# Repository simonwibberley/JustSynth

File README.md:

# JustSynth
Just Intonation Polyphonic Synthesizer

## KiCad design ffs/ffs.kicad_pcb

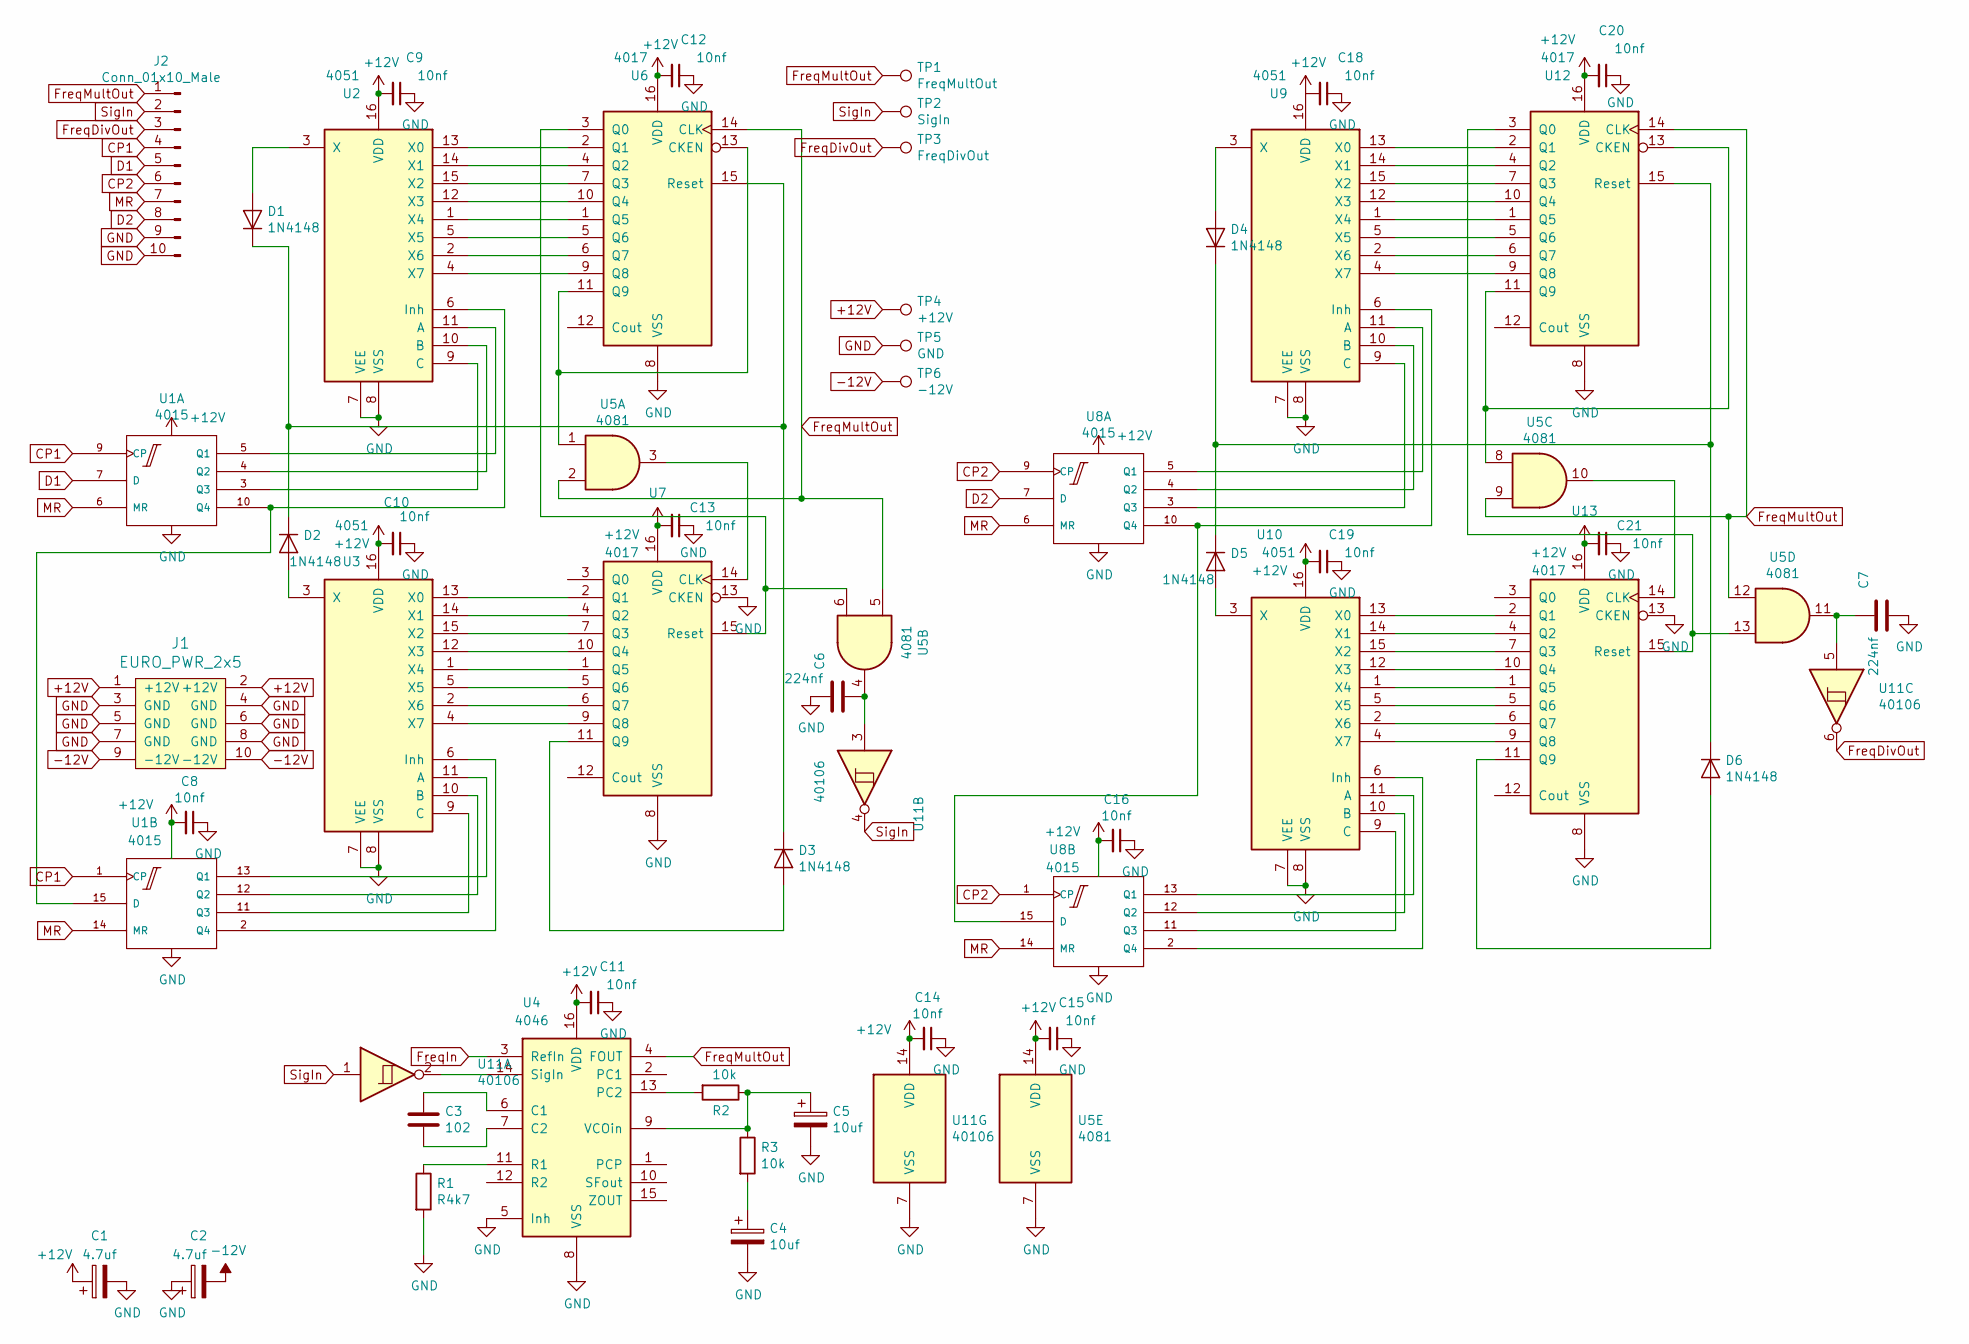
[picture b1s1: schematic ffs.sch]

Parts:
C1, C2: 4.7uf; CP_Radial_D8.0mm_P2.50mm
C3: 102; C_Disc_D4.3mm_W1.9mm_P5.00mm
C4, C5: 10uf; CP_Radial_D8.0mm_P2.50mm
C6, C7: 224nf; C_Disc_D4.3mm_W1.9mm_P5.00mm
C8, C9, C10, C11, C12, C13, C14, C15, C16, C18, C19, C20, C21: 10nf; C_1206_3216Metric_Pad1.42x1.75mm_HandSolder
D1, D2, D3, D4, D5, D6: 1N4148; D_DO-35_SOD27_P7.62mm_Horizontal
J1: EURO_PWR_2x5; IDC-Header_2x05_P2.54mm_Vertical
J2: Conn_01x10_Male; IDC-Header_2x05_P2.54mm_Vertical
R1: R4k7; R_Axial_DIN0207_L6.3mm_D2.5mm_P10.16mm_Horizontal
R2, R3: 10k; R_Axial_DIN0207_L6.3mm_D2.5mm_P10.16mm_Horizontal
TP1: FreqMultOut; TestPoint_Pad_2.5x2.5mm
TP2: SigIn; TestPoint_Pad_2.5x2.5mm
TP3: FreqDivOut; TestPoint_Pad_2.5x2.5mm
TP4: +12V; TestPoint_Pad_2.5x2.5mm
TP5: GND; TestPoint_Pad_2.5x2.5mm
TP6: -12V; TestPoint_Pad_2.5x2.5mm
U1, U8: 4015; DIP-16_W7.62mm_Socket
U2, U3, U9, U10: 4051; DIP-16_W7.62mm_Socket
U4: 4046; DIP-16_W7.62mm_Socket
U5: 4081; DIP-14_W7.62mm_Socket
U6, U7, U12, U13: 4017; DIP-16_W7.62mm_Socket
U11: 40106; DIP-16_W7.62mm_Socket

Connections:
+12V: C1.1, C8.2, C9.2, C10.2, C11.2, C12.2, C13.2, C14.2, C15.2, C16.2, C18.2, C19.2, C20.2, C21.2, J1.1 (+12V), J1.2 (+12V), TP4.1, U1.16 (Vdd), U2.16 (VDD), U3.16 (VDD), U4.16 (VDD), U5.14 (VDD), U6.16 (VDD), U7.16 (VDD), U8.16 (Vdd), U9.16 (VDD), U10.16 (VDD), U11.14 (VDD), U12.16 (VDD), U13.16 (VDD)
-12V: C2.2, J1.9 (-12V), J1.10 (-12V), TP6.1
CP1: J2.4, U1.1 (CP), U1.9 (CP)
CP2: J2.6, U8.1 (CP), U8.9 (CP)
D1: J2.5, U1.7 (D)
D2: J2.8, U8.7 (D)
FreqDivOut: J2.3, TP3.1, U11.6
FreqIn: U4.3 (RefIn)
FreqMultOut: J2.1, TP1.1, U4.4 (FOUT), U5.2, U5.5, U5.9, U5.12, U6.14 (CLK), U12.14 (CLK)
GND: C1.2, C2.1, C4.2, C5.2, C6.2, C7.1, C8.1, C9.1, C10.1, C11.1, C12.1, C13.1, C14.1, C15.1, C16.1, C18.1, C19.1, C20.1, C21.1, J1.3 (GND), J1.4 (GND), J1.5 (GND), J1.6 (GND), J1.7 (GND), J1.8 (GND), J2.9, J2.10, R1.2, TP5.1, U1.8 (Vss), U2.7 (VEE), U2.8 (VSS), U3.7 (VEE), U3.8 (VSS), U4.5 (Inh), U4.8 (VSS), U5.7 (VSS), U6.8 (VSS), U7.8 (VSS), U7.13 (CKEN), U8.8 (Vss), U9.7 (VEE), U9.8 (VSS), U10.7 (VEE), U10.8 (VSS), U11.7 (VSS), U12.8 (VSS), U13.8 (VSS), U13.13 (CKEN)
MR: J2.7, U1.6 (MR), U1.14 (MR), U8.6 (MR), U8.14 (MR)
unnamed: C3.1, U4.6 (C1)
unnamed: C3.2, U4.7 (C2)
unnamed: C4.1, R3.2
unnamed: C5.1, R2.1, R3.1, U4.9 (VCOin)
unnamed: C6.1, U5.4, U11.3
unnamed: C7.2, U5.11, U11.5
unnamed: D1.1 (K), D2.1 (K), D3.1 (K), U6.15 (Reset)
unnamed: D1.2 (A), U2.3 (X)
unnamed: D2.2 (A), U3.3 (X)
unnamed: D3.2 (A), U7.11 (Q9)
unnamed: D4.1 (K), D5.1 (K), D6.1 (K), U12.15 (Reset)
unnamed: D4.2 (A), U9.3 (X)
unnamed: D5.2 (A), U10.3 (X)
unnamed: D6.2 (A), U13.11 (Q9)
unnamed: R1.1, U4.11 (R1)
unnamed: R2.2, U4.13 (PC2)
unnamed: U1.2 (Q4), U3.6 (Inh)
unnamed: U1.3 (Q3), U2.9 (C)
unnamed: U1.4 (Q2), U2.10 (B)
unnamed: U1.5 (Q1), U2.11 (A)
unnamed: U1.10 (Q4), U1.15 (D), U2.6 (Inh)
unnamed: U1.11 (Q3), U3.9 (C)
unnamed: U1.12 (Q2), U3.10 (B)
unnamed: U1.13 (Q1), U3.11 (A)
unnamed: U2.1 (X4), U6.1 (Q5)
unnamed: U2.2 (X6), U6.6 (Q7)
unnamed: U2.4 (X7), U6.9 (Q8)
unnamed: U2.5 (X5), U6.5 (Q6)
unnamed: U2.12 (X3), U6.10 (Q4)
unnamed: U2.13 (X0), U6.2 (Q1)
unnamed: U2.14 (X1), U6.4 (Q2)
unnamed: U2.15 (X2), U6.7 (Q3)
unnamed: U3.1 (X4), U7.1 (Q5)
unnamed: U3.2 (X6), U7.6 (Q7)
unnamed: U3.4 (X7), U7.9 (Q8)
unnamed: U3.5 (X5), U7.5 (Q6)
unnamed: U3.12 (X3), U7.10 (Q4)
unnamed: U3.13 (X0), U7.2 (Q1)
unnamed: U3.14 (X1), U7.4 (Q2)
unnamed: U3.15 (X2), U7.7 (Q3)
unnamed: U5.1, U6.11 (Q9), U6.13 (CKEN)
unnamed: U5.3, U7.14 (CLK)
unnamed: U5.6, U6.3 (Q0), U7.15 (Reset)
unnamed: U8.3 (Q3), U9.9 (C)
unnamed: U8.4 (Q2), U9.10 (B)
unnamed: U8.5 (Q1), U9.11 (A)
unnamed: U8.10 (Q4), U8.15 (D), U9.6 (Inh)
unnamed: U10.1 (X4), U13.1 (Q5)
unnamed: U10.2 (X6), U13.6 (Q7)
unnamed: U10.4 (X7), U13.9 (Q8)
unnamed: U10.5 (X5), U13.5 (Q6)
unnamed: U8.2 (Q4), U10.6 (Inh)
unnamed: U8.11 (Q3), U10.9 (C)
unnamed: U8.12 (Q2), U10.10 (B)
unnamed: U8.13 (Q1), U10.11 (A)
unnamed: U10.12 (X3), U13.10 (Q4)
unnamed: U10.13 (X0), U13.2 (Q1)
unnamed: U10.14 (X1), U13.4 (Q2)
unnamed: U10.15 (X2), U13.7 (Q3)
unnamed: U4.14 (SigIn), U11.2
unnamed: U9.1 (X4), U12.1 (Q5)
unnamed: U9.13 (X0), U12.2 (Q1)
unnamed: U5.13, U12.3 (Q0), U13.15 (Reset)
unnamed: U9.14 (X1), U12.4 (Q2)
unnamed: U9.5 (X5), U12.5 (Q6)
unnamed: U9.2 (X6), U12.6 (Q7)
unnamed: U9.15 (X2), U12.7 (Q3)
unnamed: U9.4 (X7), U12.9 (Q8)
unnamed: U9.12 (X3), U12.10 (Q4)
unnamed: U5.8, U12.11 (Q9), U12.13 (CKEN)
unnamed: U5.10, U13.14 (CLK)
SigIn: J2.2, TP2.1, U11.1, U11.4

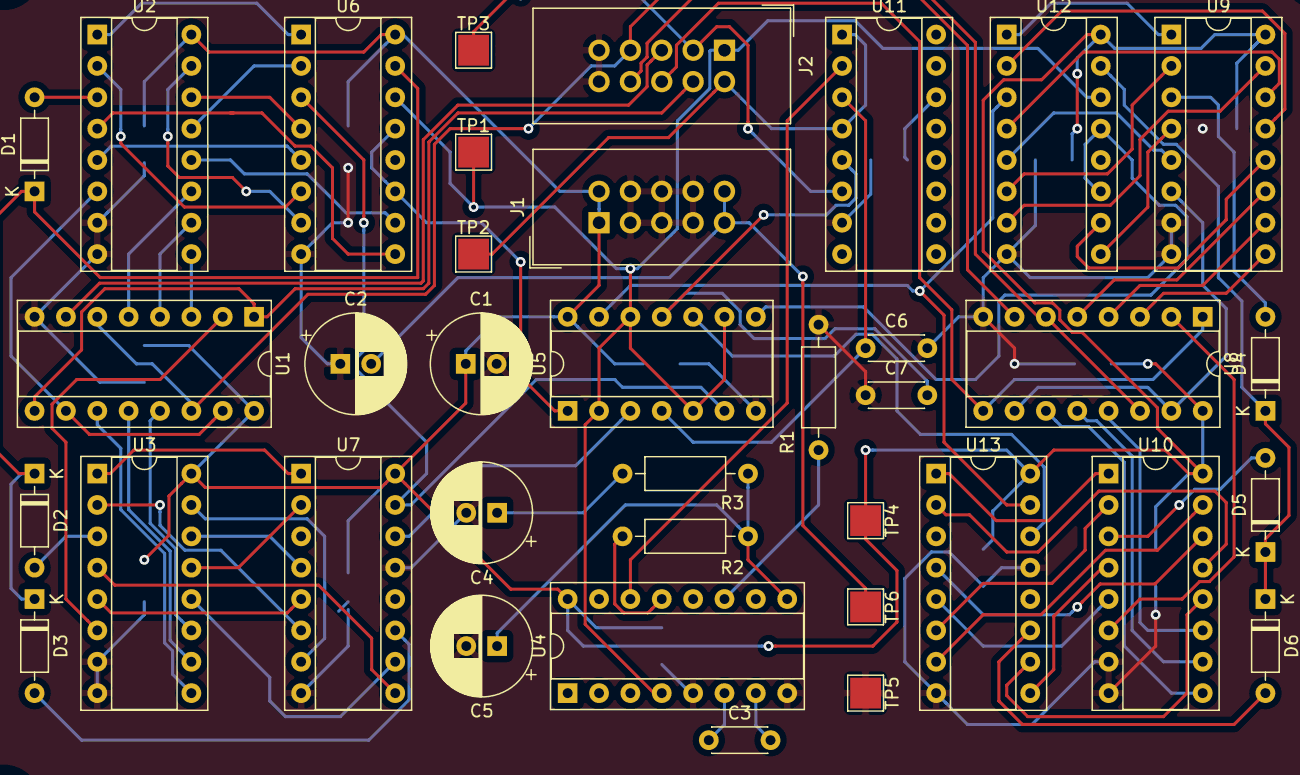
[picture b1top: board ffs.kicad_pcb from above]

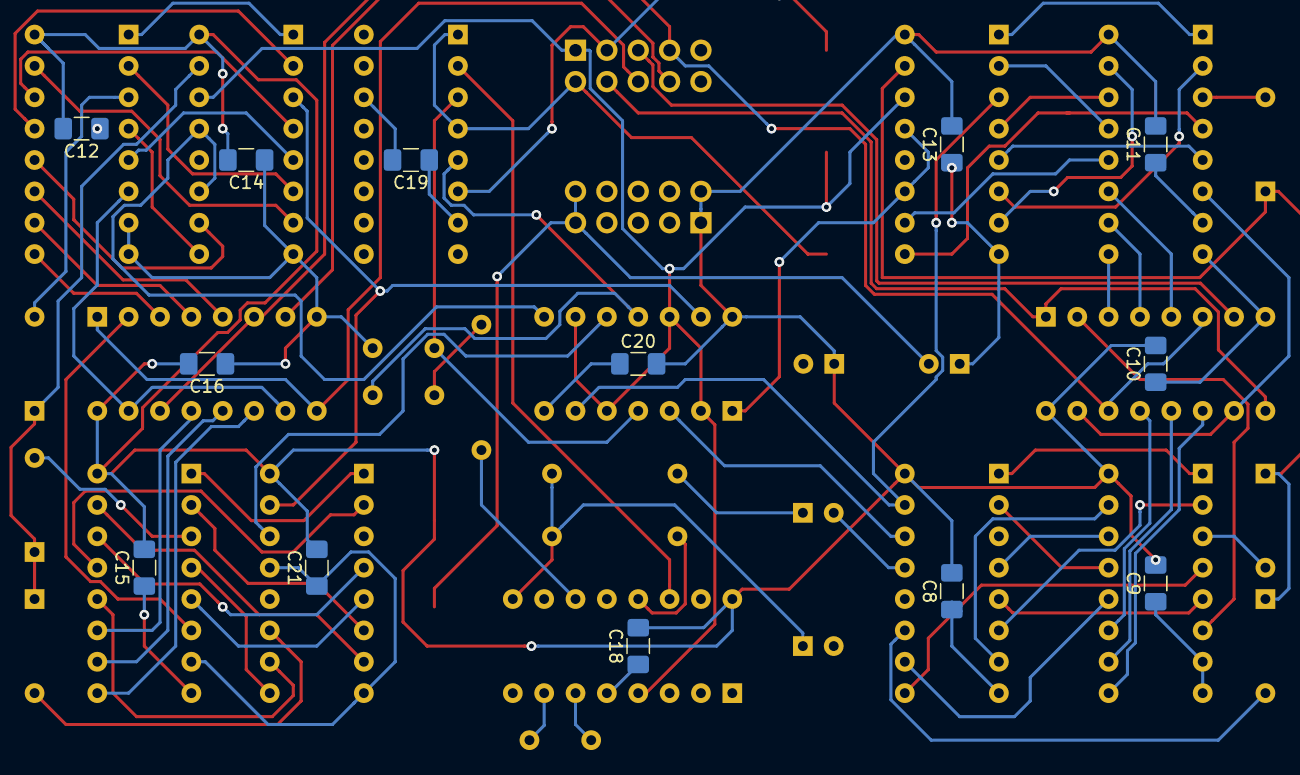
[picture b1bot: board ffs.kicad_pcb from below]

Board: 2 copper layers, 50 parts (13 on the bottom side), 82 nets.

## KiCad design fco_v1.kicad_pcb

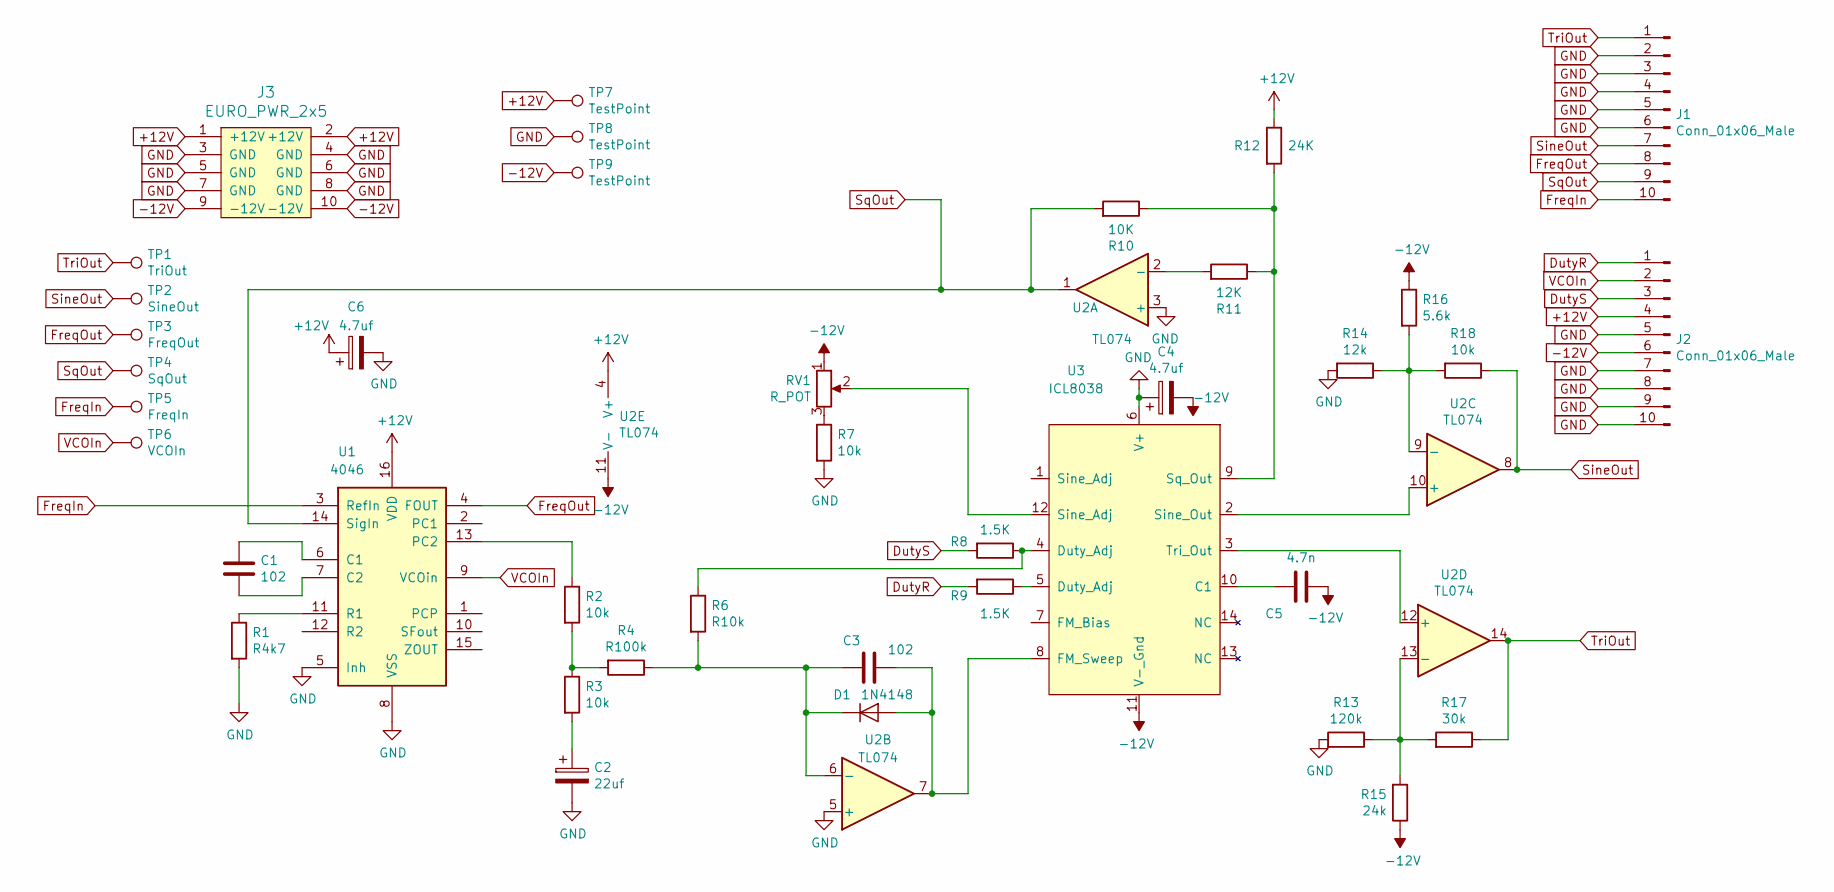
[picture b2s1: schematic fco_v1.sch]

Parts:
C1, C3: 102; C_Disc_D4.3mm_W1.9mm_P5.00mm
C2: 22uf; CP_Radial_D8.0mm_P2.50mm
C4, C6: 4.7uf; CP_Radial_D8.0mm_P2.50mm
C5: 4.7n; C_Disc_D4.3mm_W1.9mm_P5.00mm
D1: 1N4148; D_DO-35_SOD27_P7.62mm_Horizontal
J1, J2: Conn_01x06_Male; IDC-Header_2x05_P2.54mm_Vertical
J3: EURO_PWR_2x5; IDC-Header_2x05_P2.54mm_Vertical
R1: R4k7; R_Axial_DIN0207_L6.3mm_D2.5mm_P10.16mm_Horizontal
R2, R3, R7, R18: 10k; R_Axial_DIN0207_L6.3mm_D2.5mm_P10.16mm_Horizontal
R4: R100k; R_Axial_DIN0207_L6.3mm_D2.5mm_P10.16mm_Horizontal
R6: R10k; R_Axial_DIN0207_L6.3mm_D2.5mm_P10.16mm_Horizontal
R8, R9: 1.5K; R_Axial_DIN0207_L6.3mm_D2.5mm_P10.16mm_Horizontal
R10: 10K; R_Axial_DIN0207_L6.3mm_D2.5mm_P10.16mm_Horizontal
R11: 12K; R_Axial_DIN0207_L6.3mm_D2.5mm_P10.16mm_Horizontal
R12: 24K; R_Axial_DIN0207_L6.3mm_D2.5mm_P10.16mm_Horizontal
R13: 120k; R_Axial_DIN0207_L6.3mm_D2.5mm_P10.16mm_Horizontal
R14: 12k; R_Axial_DIN0207_L6.3mm_D2.5mm_P10.16mm_Horizontal
R15: 24k; R_Axial_DIN0207_L6.3mm_D2.5mm_P10.16mm_Horizontal
R16: 5.6k; R_Axial_DIN0207_L6.3mm_D2.5mm_P10.16mm_Horizontal
R17: 30k; R_Axial_DIN0207_L6.3mm_D2.5mm_P10.16mm_Horizontal
RV1: R_POT; Potentiometer_Bourns_3296W_Vertical
TP1: TriOut; TestPoint_Pad_2.5x2.5mm
TP2: SineOut; TestPoint_Pad_2.5x2.5mm
TP3: FreqOut; TestPoint_Pad_2.5x2.5mm
TP4: SqOut; TestPoint_Pad_2.5x2.5mm
TP5: FreqIn; TestPoint_Pad_2.5x2.5mm
TP6: VCOIn; TestPoint_Pad_2.5x2.5mm
TP7, TP8, TP9: TestPoint; TestPoint_Pad_2.5x2.5mm
U1: 4046; DIP-16_W7.62mm_Socket
U2: TL074; DIP-14_W7.62mm_Socket
U3: ICL8038; DIP-14_W7.62mm_Socket

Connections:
+12V: C6.1, J2.4, J3.1 (+12V), J3.2 (+12V), R12.1, TP7.1, U1.16 (VDD), U2.4 (V+)
-12V: C4.2, C5.1, J2.6, J3.9 (-12V), J3.10 (-12V), R15.1, R16.1, RV1.1, TP9.1, U2.11 (V-), U3.11 (V-_Gnd)
DutyR: J2.1, R9.2
DutyS: J2.3, R8.2
FreqIn: J1.10, TP5.1, U1.3 (RefIn)
FreqOut: J1.8, TP3.1, U1.4 (FOUT)
GND: C2.2, C4.1, C6.2, J1.2, J1.3, J1.4, J1.5, J1.6, J2.5, J2.7, J2.8, J2.9, J2.10, J3.3 (GND), J3.4 (GND), J3.5 (GND), J3.6 (GND), J3.7 (GND), J3.8 (GND), R1.2, R7.2, R13.2, R14.2, TP8.1, U1.5 (Inh), U1.8 (VSS), U2.3 (+), U2.5 (+), U3.6 (V+)
unnamed: C1.1, U1.6 (C1)
unnamed: C1.2, U1.7 (C2)
unnamed: C2.1, R3.2
unnamed: C3.1, D1.2 (A), U2.7, U3.8 (FM_Sweep)
unnamed: C3.2, D1.1 (K), R4.1, R6.2, U2.6 (-)
unnamed: C5.2, U3.10 (C1)
unnamed: R1.1, U1.11 (R1)
unnamed: R2.1, U1.13 (PC2)
unnamed: R2.2, R3.1, R4.2
unnamed: R6.1, R8.1, U3.4 (Duty_Adj)
unnamed: R7.1, RV1.3
unnamed: R9.1, U3.5 (Duty_Adj)
unnamed: R10.1, R11.1, R12.2, U3.9 (Sq_Out)
unnamed: R11.2, U2.2 (-)
unnamed: R13.1, R15.2, R17.2, U2.13 (-)
unnamed: R14.1, R16.2, R18.2, U2.9 (-)
unnamed: RV1.2, U3.12 (Sine_Adj)
unnamed: U2.10 (+), U3.2 (Sine_Out)
unnamed: U2.12 (+), U3.3 (Tri_Out)
SineOut: J1.7, R18.1, TP2.1, U2.8
SqOut: J1.9, R10.2, TP4.1, U1.14 (SigIn), U2.1
TriOut: J1.1, R17.1, TP1.1, U2.14
VCOIn: J2.2, TP6.1, U1.9 (VCOin)

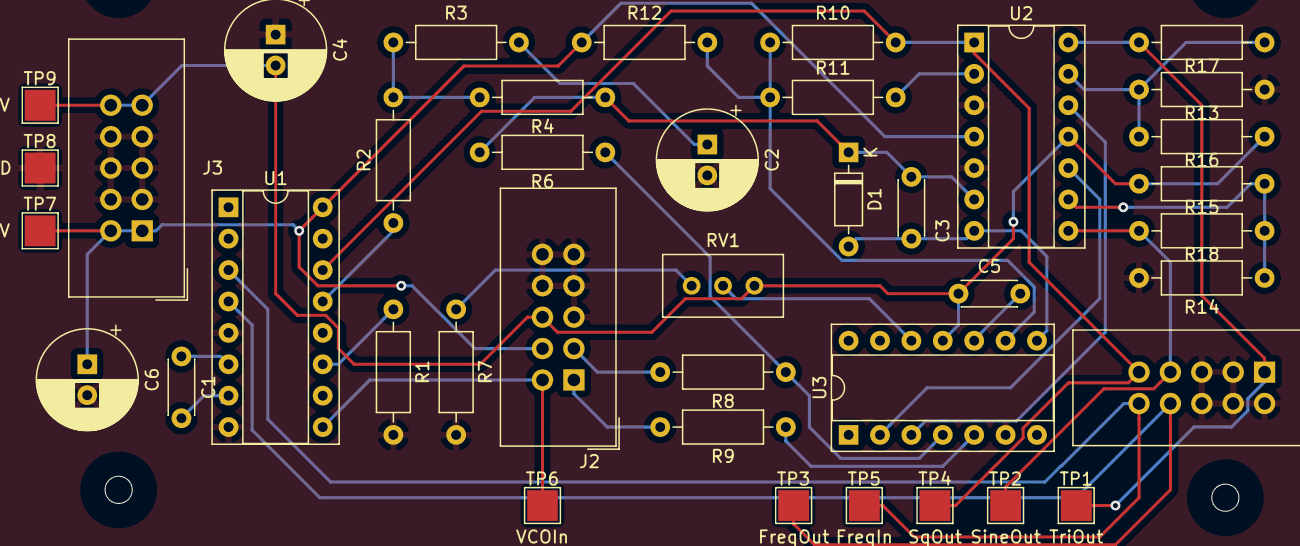
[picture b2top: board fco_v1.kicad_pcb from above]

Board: 2 copper layers, 40 parts (0 on the bottom side), 30 nets.

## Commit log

2020-01-28 inital commit
2020-01-28 mv'd fco to sub dir
2020-01-28 and gerber
2020-01-29 added initial FFS 4000
2020-01-31 added button controlled controller, fixed multiplier circuit
2020-02-12 ffs routing done
2020-03-01 added bypass caps
